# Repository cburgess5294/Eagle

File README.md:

# Eagle
Repository for Shared Eagle CAD Projects

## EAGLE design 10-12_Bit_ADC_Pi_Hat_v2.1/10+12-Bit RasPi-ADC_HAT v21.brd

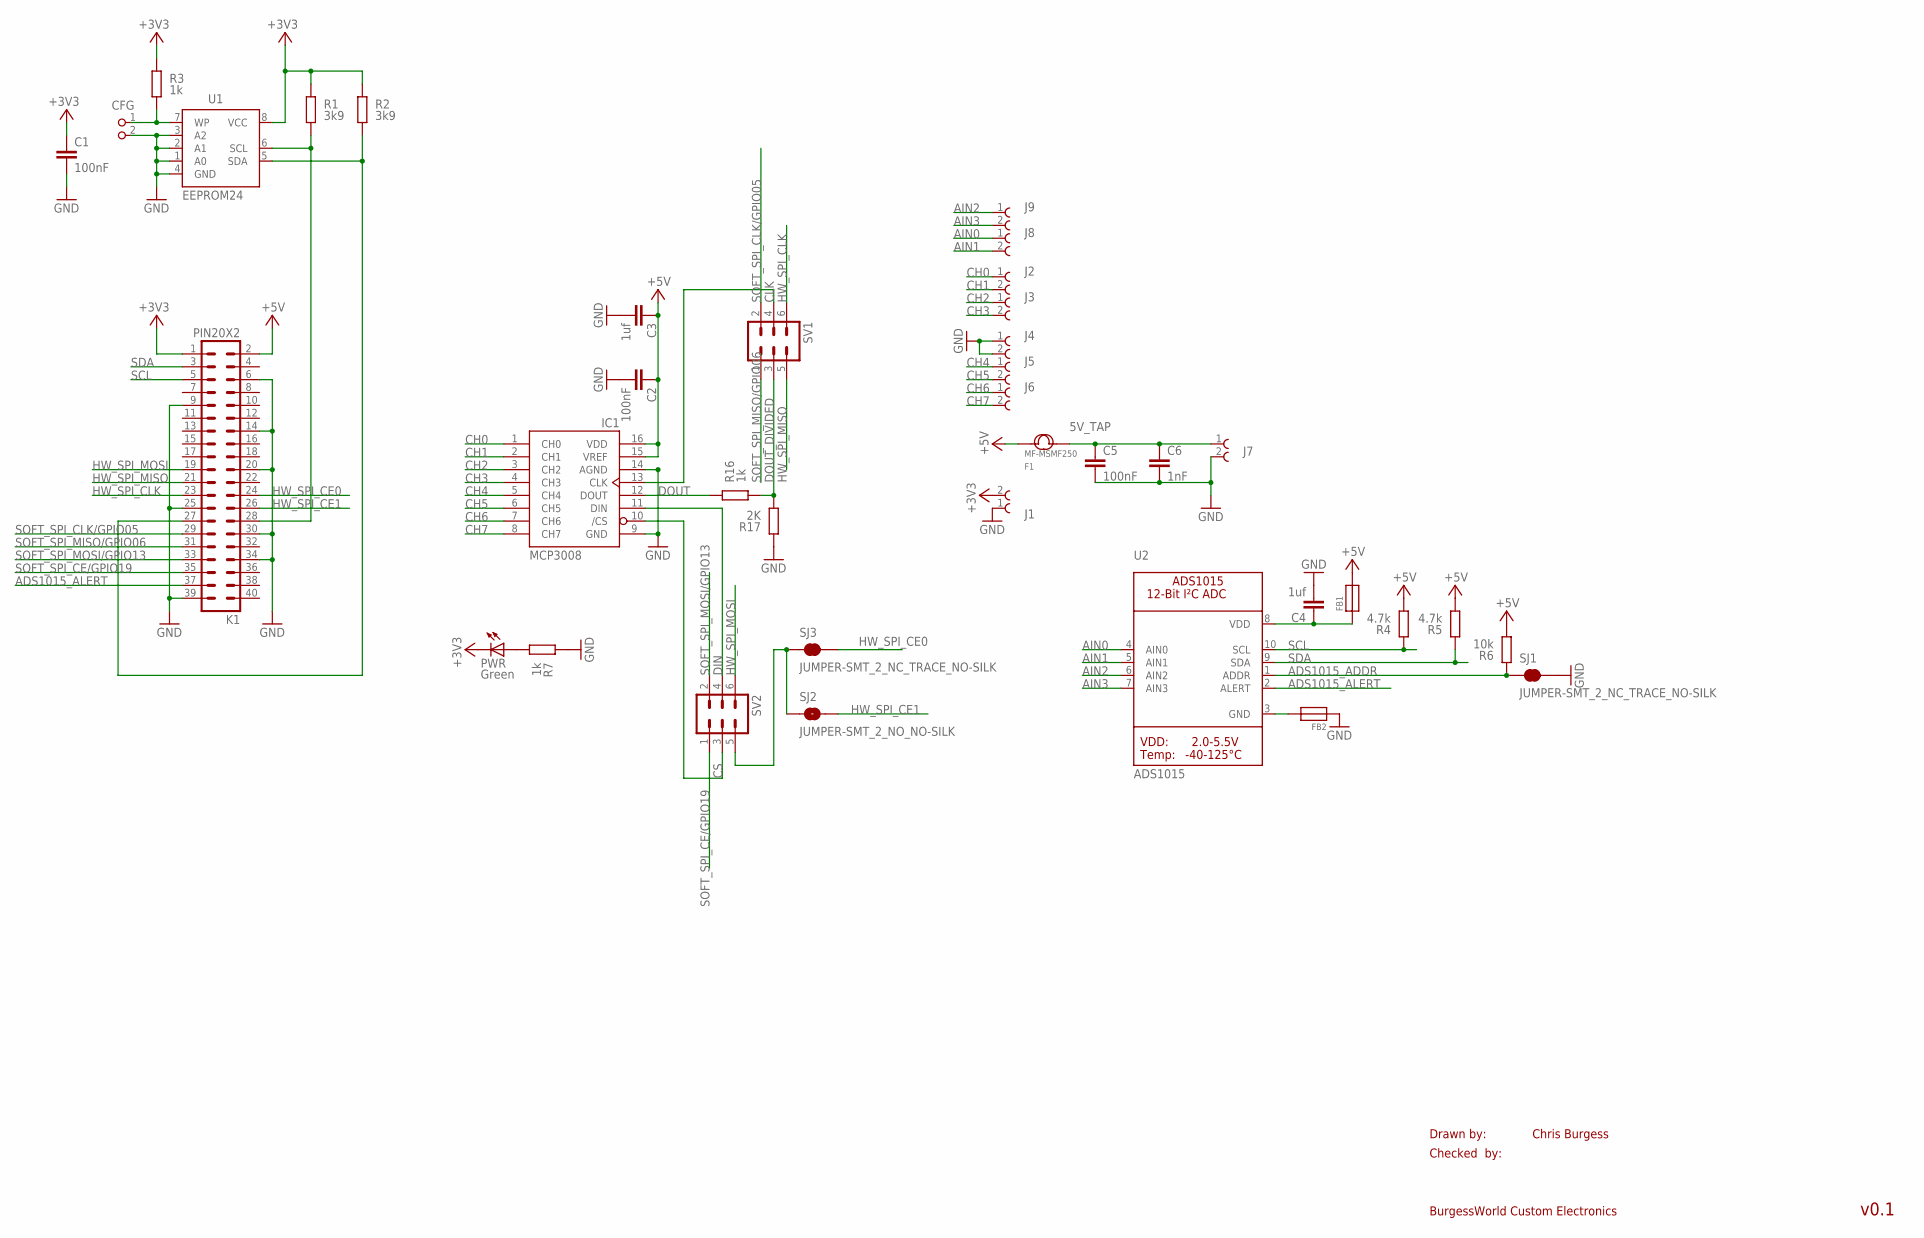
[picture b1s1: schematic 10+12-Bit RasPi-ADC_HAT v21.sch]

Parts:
C1, C2, C5: 100nF; C0805K
C3, C4: 1uf; C0805K
C6: 1nF; C0805K
CFG: PIN2_100; PIN_W_2
F1: MF-MSMF250; F1812
FB1, FB2: FERRITE0805; 0805
IC1: MCP3008; DIL16
J1, J2, J3, J4, J5, J6, J7, J8, J9: 691214110002
K1: PIN20X2; PIN_20X2
PWR: Green; CHIPLED_0805
R1, R2: 3k9; M0805; TOLERANCE 5%
R3, R7, R16: 1k; M0805; TOLERANCE 5%
R4, R5: 4.7k; M0805; TOLERANCE 5%
R6: 10k; M0805; TOLERANCE 5%
R17: 2K; M0805; TOLERANCE 5%
SJ1, SJ3: JUMPER-SMT_2_NC_TRACE_NO-SILK; SMT-JUMPER_2_NC_TRACE_NO-SILK
SJ2: JUMPER-SMT_2_NO_NO-SILK; SMT-JUMPER_2_NO_NO-SILK
SV1, SV2: MA03-2
U1: EEPROM24; SOIC8
U2: ADS1015; MSOP10

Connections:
5V_TAP: C5.1, C6.1, F1.2, J7.1
+3V3: C1.1, J1.2, K1.1, PWR.C, R1.2, R2.2, R3.2, U1.8 (VCC)
+5V: C2.1, C3.1, F1.1, FB1.2, IC1.15 (VREF), IC1.16 (VDD), K1.2, R4.1, R5.1, R6.1
ADS1015_ADDR: R6.2, SJ1.1, U2.1 (ADDR)
ADS1015_ALERT: K1.37, U2.2 (ALERT)
ADS1015_FB: FB2.2, U2.3 (GND)
ADS1015_VDD: C4.1, FB1.1, U2.8 (VDD)
AIN0: J8.1, U2.4 (AIN0)
AIN1: J8.2, U2.5 (AIN1)
AIN2: J9.1, U2.6 (AIN2)
AIN3: J9.2, U2.7 (AIN3)
CH0: IC1.1 (CH0), J2.1
CH1: IC1.2 (CH1), J2.2
CH2: IC1.3 (CH2), J3.1
CH3: IC1.4 (CH3), J3.2
CH4: IC1.5 (CH4), J5.1
CH5: IC1.6 (CH5), J5.2
CH6: IC1.7 (CH6), J6.1
CH7: IC1.8 (CH7), J6.2
CLK: IC1.13 (CLK), SV1.4
CS: IC1.10 (/CS), SV2.3
DIN: IC1.11 (DIN), SV2.4
DOUT: IC1.12 (DOUT), R16.2
DOUT_DIVIDED: R16.1, R17.1, SV1.3
EEPROM_PROG: CFG.1, R3.1, U1.7 (WP)
GND: C1.2, C2.2, C3.2, C4.2, C5.2, C6.2, CFG.2, FB2.1, IC1.9 (GND), IC1.14 (AGND), J1.1, J4.1, J4.2, J7.2, K1.6, K1.9, K1.14, K1.20, K1.25, K1.30, K1.34, K1.39, R7.2, R17.2, SJ1.2, U1.1 (A0), U1.2 (A1), U1.3 (A2), U1.4 (GND)
HW_SPI_CE: SJ2.1, SJ3.1, SV2.5
HW_SPI_CE0: K1.24, SJ3.2
HW_SPI_CE1: K1.26, SJ2.2
HW_SPI_CLK: K1.23, SV1.6
HW_SPI_MISO: K1.21, SV1.5
HW_SPI_MOSI: K1.19, SV2.6
ID_SC_27: K1.27, R2.1, U1.5 (SDA)
ID_SC_28: K1.28, R1.1, U1.6 (SCL)
unnamed: PWR.A, R7.1
SCL: K1.5, R4.2, U2.10 (SCL)
SDA: K1.3, R5.2, U2.9 (SDA)
SOFT_SPI_CE/GPIO19: K1.35, SV2.1
SOFT_SPI_CLK/GPIO05: K1.29, SV1.2
SOFT_SPI_MISO/GPIO06: K1.31, SV1.1
SOFT_SPI_MOSI/GPIO13: K1.33, SV2.2

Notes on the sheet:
Drawn by:
Checked by:
BurgessWorld Custom Electronics
Chris Burgess
v0.1

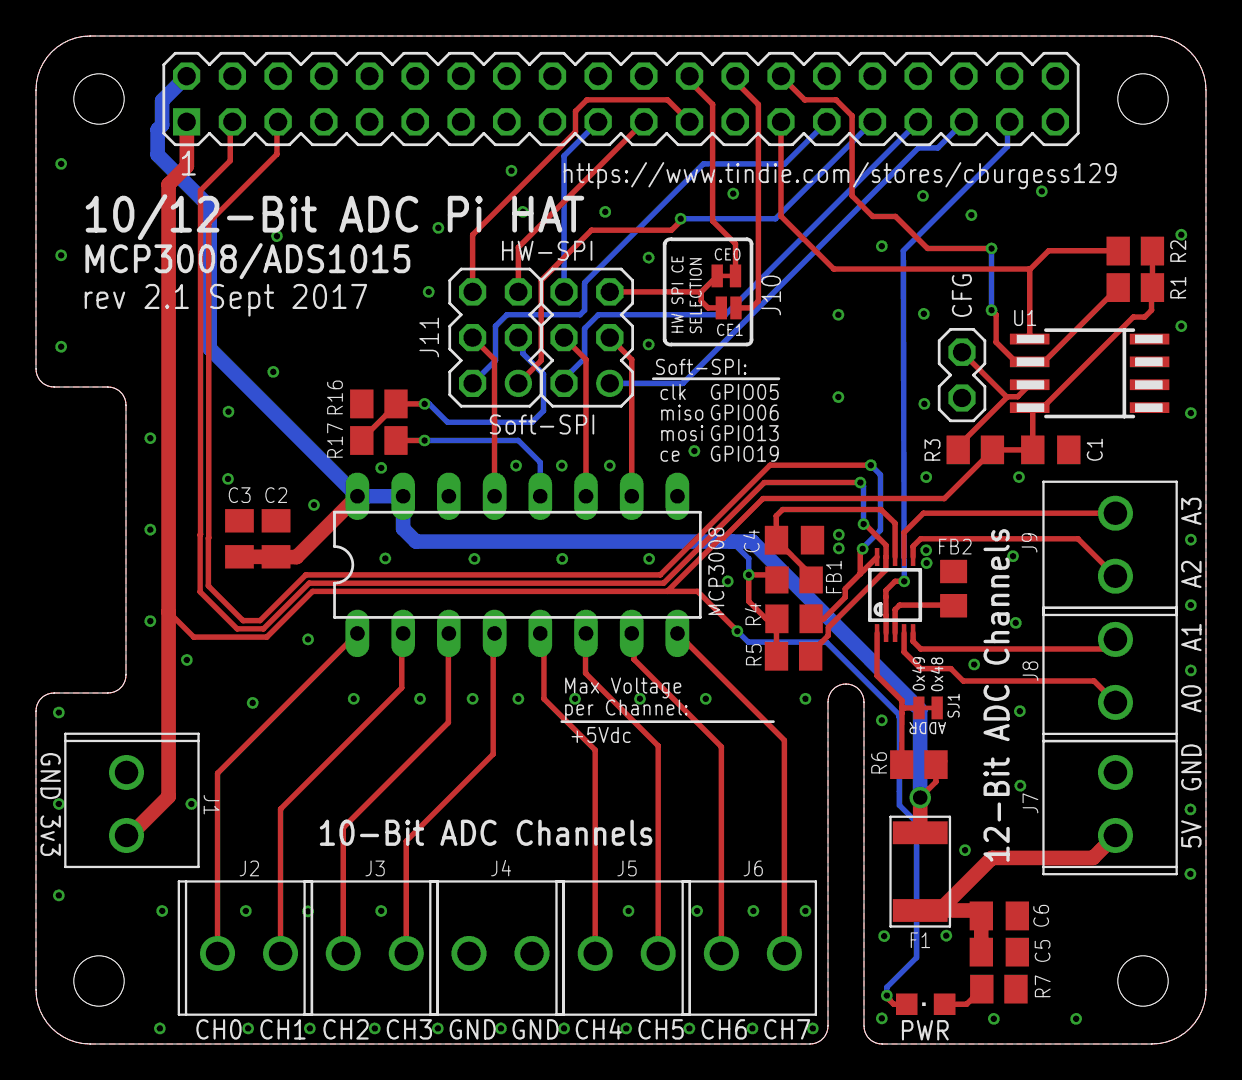
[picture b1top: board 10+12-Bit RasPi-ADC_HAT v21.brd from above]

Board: 2 copper layers, 65.0 x 56.0 mm, 38 parts (0 on the bottom side), 41 nets.

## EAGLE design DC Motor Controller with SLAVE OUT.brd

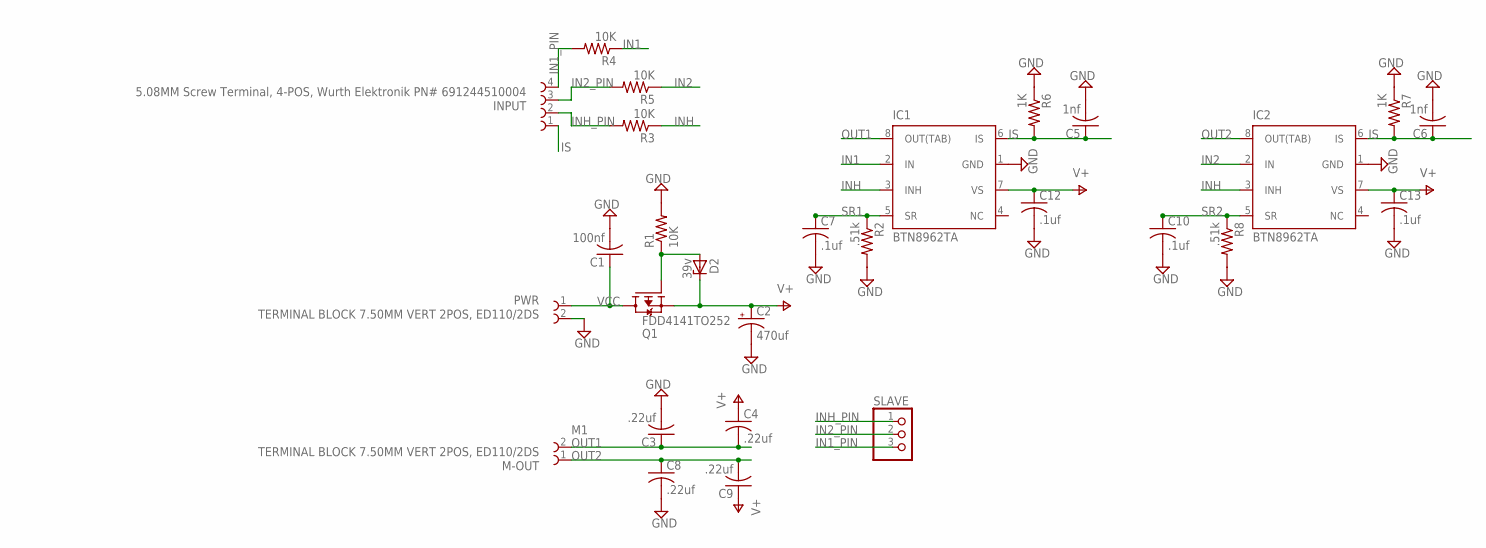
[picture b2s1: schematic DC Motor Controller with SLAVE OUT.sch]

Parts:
C1: 100nf; C0805
C2: 470uf; TT5D10
C3, C4, C8, C9: .22uf; C0805
C5, C6: 1nf; C0805
C7, C10, C12, C13: .1uf; C0805
D2: 39v; SMB
IC1, IC2: BTN8962TA; P-TO263-7-1_LG_PADS
INPUT: 5.08MM Screw Terminal, 4-POS, Wurth Elektronik PN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; 691244510004
M-OUT: TERMINAL BLOCK 7.50MM VERT 2POS, ED110/2DS; 7-5MM-SCREW-TERM
PWR: TERMINAL BLOCK 7.50MM VERT 2POS, ED110/2DS; 7-5MM-SCREW-TERM
Q1: FDD4141TO252; TO252
R1, R3, R4, R5: 10K; R0805
R2, R8: .51k; R0805
R6, R7: 1K; R0805
SLAVE: PINHD-1X3CB; 1X03-CLEANBIG

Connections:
GND: C1.2, C2.-, C3.2, C5.2, C6.2, C7.2, C8.2, C10.2, C12.2, C13.2, IC1.1 (GND), IC2.1 (GND), PWR.2, R1.2, R2.2, R6.1, R7.1, R8.2
IN1: IC1.2 (IN), R4.1
IN1_PIN: INPUT.4, R4.2, SLAVE.3
IN2: IC2.2 (IN), R5.1
IN2_PIN: INPUT.3, R5.2, SLAVE.2
INH: IC1.3 (INH), IC2.3 (INH), R3.1
INH_PIN: INPUT.2, R3.2, SLAVE.1
IS: C5.1, C6.1, IC1.6 (IS), IC2.6 (IS), INPUT.1, R6.2, R7.2
OUT1: C3.1, C4.2, IC1.8 (OUT(TAB)), M-OUT.2
OUT2: C8.1, C9.2, IC2.8 (OUT(TAB)), M-OUT.1
Q1_GATE: D2.A, Q1.1 (G), R1.1
SR1: C7.1, IC1.5 (SR), R2.1
SR2: C10.1, IC2.5 (SR), R8.1
V+: C2.+, C4.1, C9.1, C12.1, C13.1, D2.C, IC1.7 (VS), IC2.7 (VS), Q1.2 (S)
VCC: C1.1, PWR.1, Q1.3 (D)

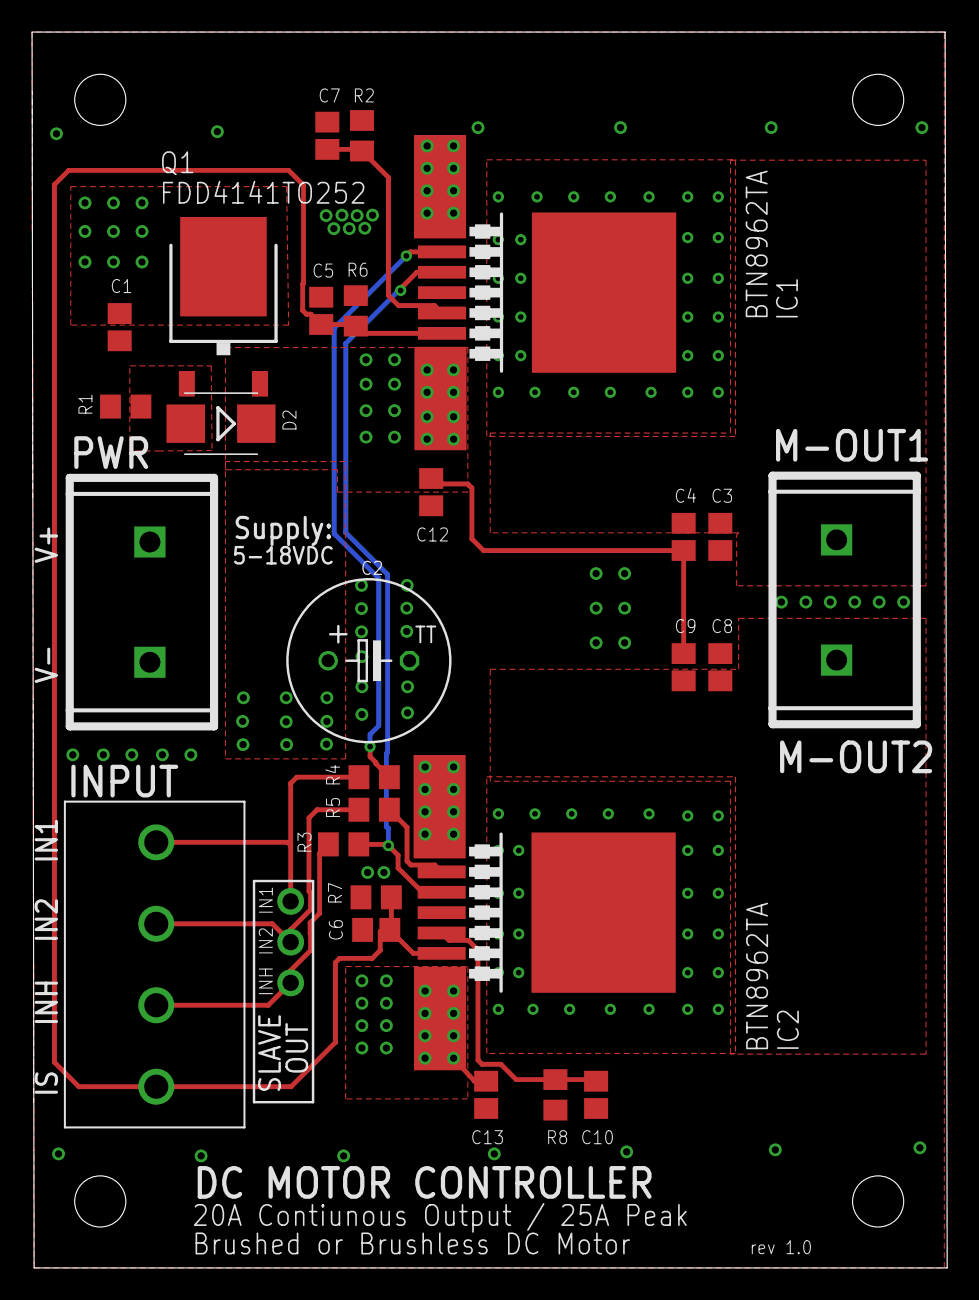
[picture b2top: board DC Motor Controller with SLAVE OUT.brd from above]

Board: 2 copper layers, 57.1 x 77.1 mm, 28 parts (0 on the bottom side), 15 nets.

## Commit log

2017-09-19 Create new file
2017-09-19 Rename DC Motor Controller with SLAVE OUT.brd to 20 DC Motor Controller/DC Motor Controller with SLAVE OUT.brd
2017-09-19 Rename DC Motor Controller with SLAVE OUT.sch to 20 DC Motor Controller/DC Motor Controller with SLAVE OUT.sch
2017-09-27 Create temp
2021-02-12 Add rev 2.6 design files

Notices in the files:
parts and their libraries:
Wurth_Elektronik_Electromechanic_Termina: Copyright: Würth Elektronik
SparkFun-Jumpers: Licensing: Creative Commons ShareAlike 4.0 International - https://creativecommons.org/licenses/by-sa/4.0
